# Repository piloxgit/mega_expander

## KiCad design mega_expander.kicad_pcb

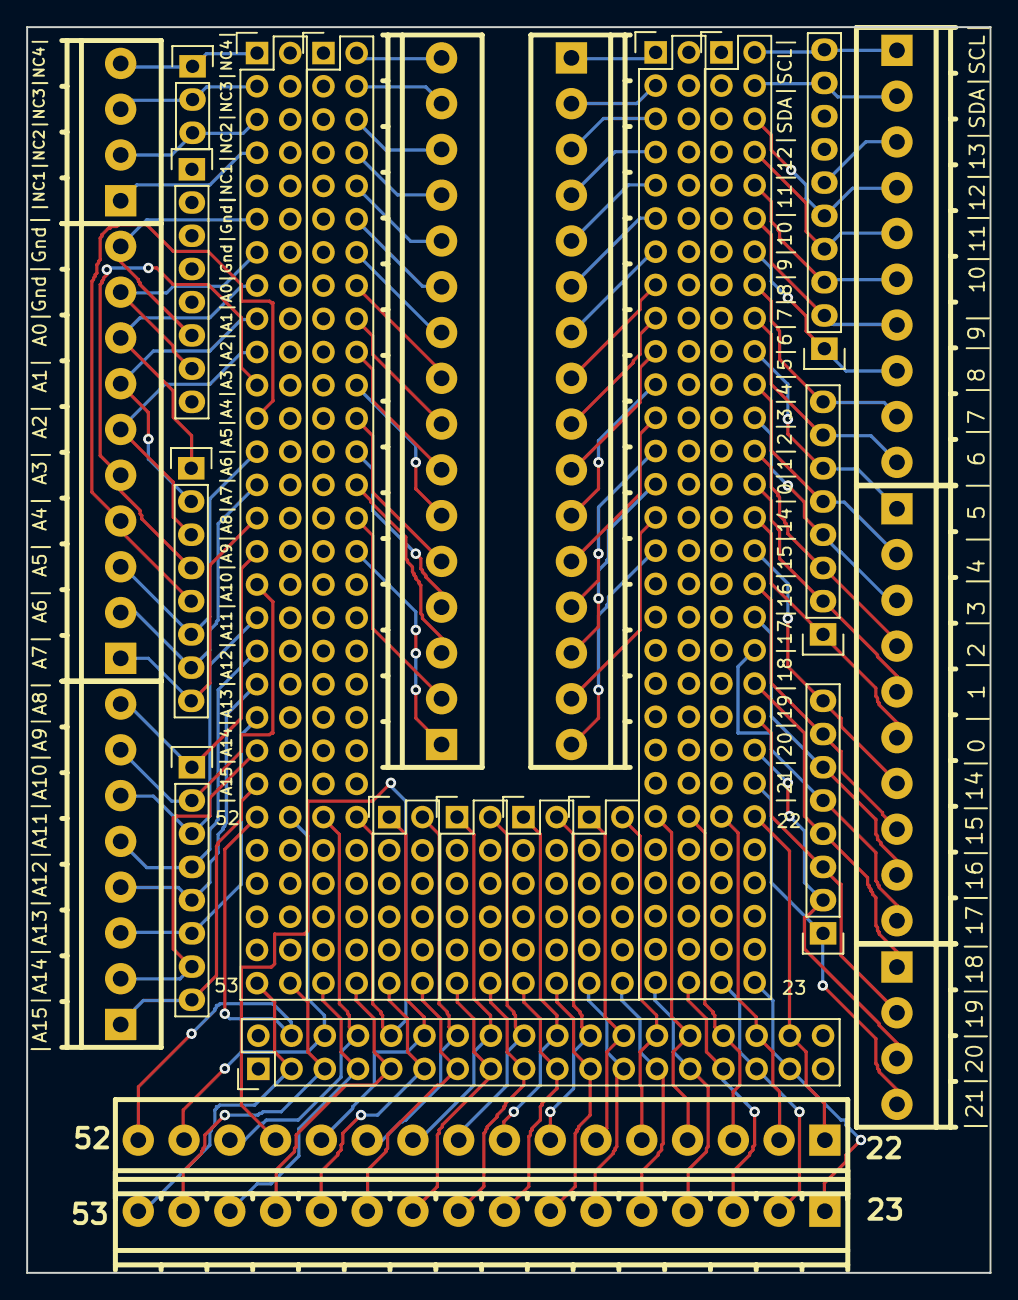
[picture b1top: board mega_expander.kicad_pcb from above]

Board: 2 copper layers, 73.7 x 95.2 mm, 17 parts (0 on the bottom side), 61 nets.

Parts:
10|11|12|13|SDA|SCL|, 52: CONN_01X08; Pin_Header_Straight_1x08
17|16|15|14|: pt_1,5-8-3,5-h
22, 23, 53: CONN_02X06; Pin_Header_Straight_2x06
22#2: pt_1,5-4-3,5-h
23#2: |A15|A14|A13|A12|A11|A10|A9|A8|A7|A6|A5|A4|A3|A2|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; pt_1,5-16-3,5-h
52#2, 53#2: pt_1,5-10-3,5-h
 0 | 1 |2 |3 |4 | 5 | 6 |7 |8 |9|: CONN_01X08; Pin_Header_Straight_1x08
Gnd|Gnd|: CONN_01X10; Pin_Header_Straight_1x10
|21|20|19|18|: CONN_02X18; Pin_Header_Straight_2x18
|21|20|19|18|17|16|15|14|0|1|2|3|4|5|6|7|8|9|10|11|12|SDA|SCL|: CONN_02X29; Pin_Header_Straight_2x29
|A15|A14|A13|A12|A11|A10|A9|A8| A7| A6| A5| A4| A3| A2| A1| A0|: CONN_01X08; Pin_Header_Straight_1x08
|NC1|NC2|NC3|NC4|: CONN_01X03; Pin_Header_Straight_1x03
|NC1|NC2|NC3|NC4|#2: CONN_02X29; Pin_Header_Straight_2x29

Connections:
unnamed: |NC1|NC2|NC3|NC4|.1, |NC1|NC2|NC3|NC4|#2.1
unnamed: |NC1|NC2|NC3|NC4|.2, |NC1|NC2|NC3|NC4|#2.3
unnamed: |NC1|NC2|NC3|NC4|.3, |NC1|NC2|NC3|NC4|#2.5
unnamed: 10|11|12|13|SDA|SCL|.6, 52#2.10, |NC1|NC2|NC3|NC4|#2.11
unnamed: 10|11|12|13|SDA|SCL|.7, 52#2.9, |NC1|NC2|NC3|NC4|#2.13
unnamed: 52#2.8, |A15|A14|A13|A12|A11|A10|A9|A8| A7| A6|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.1, |NC1|NC2|NC3|NC4|#2.15
unnamed: 52#2.7, |A15|A14|A13|A12|A11|A10|A9|A8| A7| A6|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.2, |NC1|NC2|NC3|NC4|#2.17
unnamed: 52#2.6, |A15|A14|A13|A12|A11|A10|A9|A8| A7| A6|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.3, |NC1|NC2|NC3|NC4|#2.19
unnamed: 52#2.5, |A15|A14|A13|A12|A11|A10|A9|A8| A7| A6|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.4, |NC1|NC2|NC3|NC4|#2.21
unnamed: 52#2.4, |A15|A14|A13|A12|A11|A10|A9|A8| A7| A6|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.5, |NC1|NC2|NC3|NC4|#2.23
unnamed: 52#2.3, |A15|A14|A13|A12|A11|A10|A9|A8| A7| A6|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.6, |NC1|NC2|NC3|NC4|#2.25
unnamed: 52#2.2, |A15|A14|A13|A12|A11|A10|A9|A8| A7| A6|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.7, |NC1|NC2|NC3|NC4|#2.27
unnamed: 52#2.1, |A15|A14|A13|A12|A11|A10|A9|A8| A7| A6|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.8, |NC1|NC2|NC3|NC4|#2.29
unnamed: 17|16|15|14|.8, |NC1|NC2|NC3|NC4|#2.31
unnamed: 17|16|15|14|.7, |NC1|NC2|NC3|NC4|#2.33
unnamed: 17|16|15|14|.6, |NC1|NC2|NC3|NC4|#2.35
unnamed: 17|16|15|14|.5, |NC1|NC2|NC3|NC4|#2.37
unnamed: 17|16|15|14|.4, |NC1|NC2|NC3|NC4|#2.39
unnamed: 17|16|15|14|.3, |NC1|NC2|NC3|NC4|#2.41
unnamed: 17|16|15|14|.2, |NC1|NC2|NC3|NC4|#2.43
unnamed: 17|16|15|14|.1, |NC1|NC2|NC3|NC4|#2.45
unnamed: |21|20|19|18|.4, |NC1|NC2|NC3|NC4|#2.47
unnamed: |21|20|19|18|.6, |NC1|NC2|NC3|NC4|#2.48
unnamed: 23#2.16, |21|20|19|18|.3, |NC1|NC2|NC3|NC4|#2.57
unnamed: 23#2.15, |21|20|19|18|.5, |NC1|NC2|NC3|NC4|#2.58
unnamed: |21|20|19|18|.8, |21|20|19|18|17|16|15|14|0|1|2|3|4|5|6|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.47
unnamed: |21|20|19|18|.10, |21|20|19|18|17|16|15|14|0|1|2|3|4|5|6|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.48
unnamed: 23#2.14, |21|20|19|18|.7, |21|20|19|18|17|16|15|14|0|1|2|3|4|5|6|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.57
unnamed: 23#2.13, |21|20|19|18|.9, |21|20|19|18|17|16|15|14|0|1|2|3|4|5|6|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.58
unnamed: 53.1, |21|20|19|18|.12
unnamed: 53.2, |21|20|19|18|.14
unnamed: 23#2.12, 53.11, |21|20|19|18|.11
unnamed: 23#2.11, 53.12, |21|20|19|18|.13
unnamed: 23#2.10, |21|20|19|18|.15
unnamed: 23#2.9, |21|20|19|18|.17
unnamed: 22.1, |21|20|19|18|.20
unnamed: 22.2, |21|20|19|18|.22
unnamed: 22.11, 23#2.8, |21|20|19|18|.19
unnamed: 22.12, 23#2.7, |21|20|19|18|.21
unnamed: 23.1, |21|20|19|18|.24
unnamed: 23.2, |21|20|19|18|.26
unnamed: 23.11, 23#2.6, |21|20|19|18|.23
unnamed: 23.12, 23#2.5, |21|20|19|18|.25
unnamed: 23#2.4, |21|20|19|18|.27
unnamed: 23#2.3, |21|20|19|18|.29
unnamed: 52.6, 53#2.1
unnamed: 52.5, 53#2.2
unnamed: 52.4, 53#2.3
unnamed: 52.3, 53#2.4
unnamed: 52.2, 53#2.5
unnamed: 52.1, 53#2.6
unnamed: 53#2.7, 0 | 1 |2 |3 |4 | 5 | 6 |7 |8 |9|.8
unnamed: 53#2.8, 0 | 1 |2 |3 |4 | 5 | 6 |7 |8 |9|.7
unnamed: 53#2.9, 0 | 1 |2 |3 |4 | 5 | 6 |7 |8 |9|.6
unnamed: 53#2.10, 0 | 1 |2 |3 |4 | 5 | 6 |7 |8 |9|.5
unnamed: 22#2.1, 0 | 1 |2 |3 |4 | 5 | 6 |7 |8 |9|.4
unnamed: 22#2.2, 0 | 1 |2 |3 |4 | 5 | 6 |7 |8 |9|.3
unnamed: 22#2.3, 0 | 1 |2 |3 |4 | 5 | 6 |7 |8 |9|.2
unnamed: 22#2.4, 0 | 1 |2 |3 |4 | 5 | 6 |7 |8 |9|.1
unnamed: 23#2.2, |21|20|19|18|.31
unnamed: 23#2.1, |21|20|19|18|.33

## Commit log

2017-02-03 first_pu
2017-02-03 druha
2017-02-03 treti
